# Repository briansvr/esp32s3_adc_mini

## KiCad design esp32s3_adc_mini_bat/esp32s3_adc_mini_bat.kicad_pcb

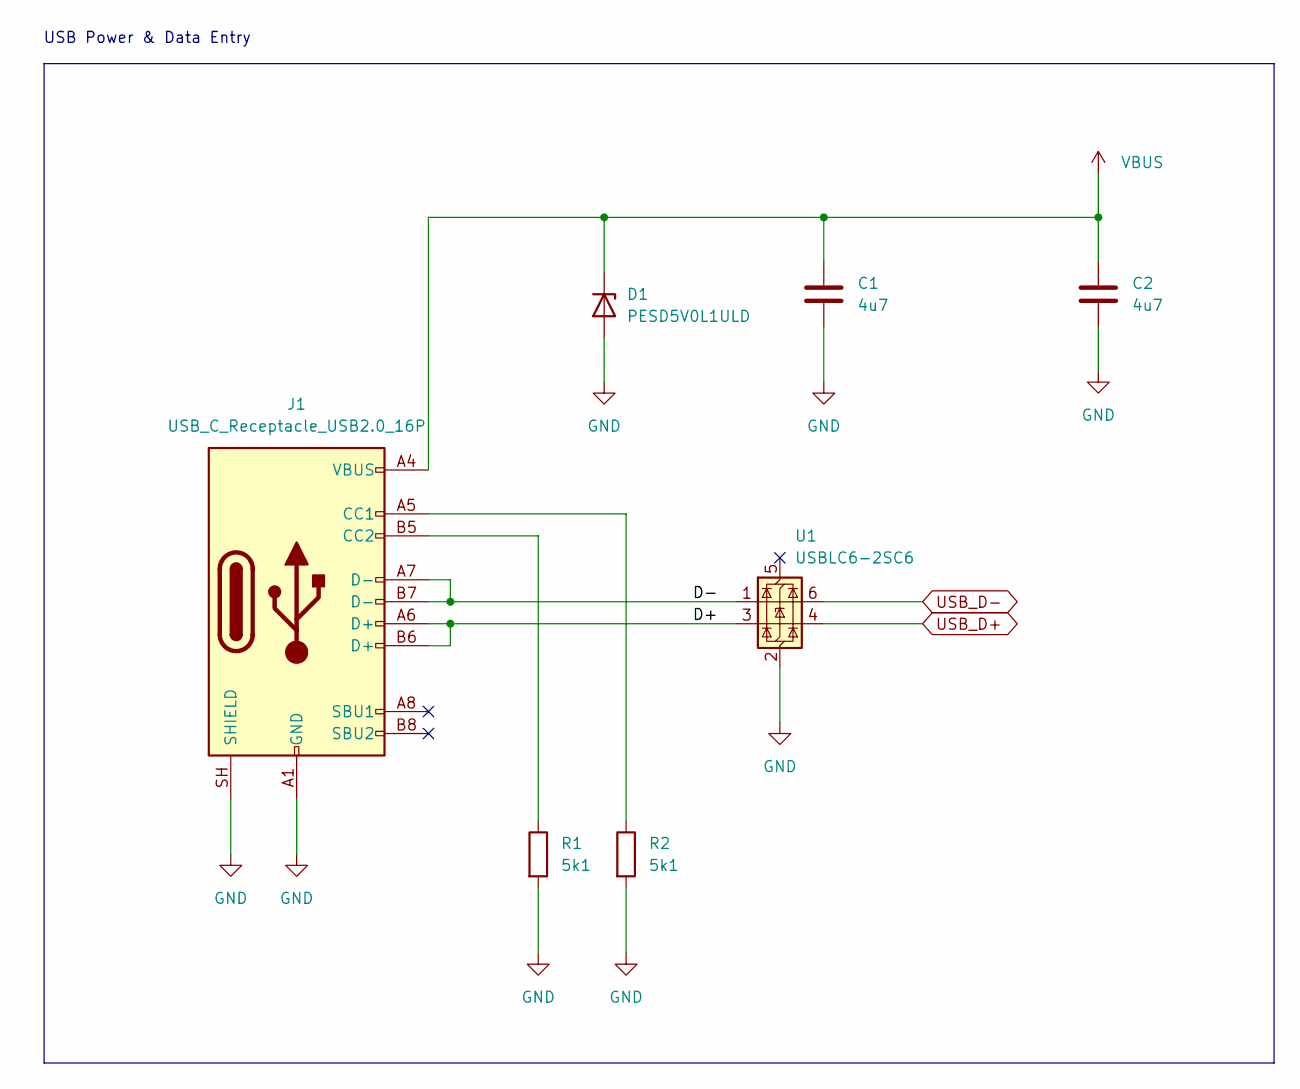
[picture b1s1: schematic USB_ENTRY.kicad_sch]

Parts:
C1, C2: 4u7; C_0805_2012Metric
D1: PESD5V0L1ULD; D_SOD-882D
J1: USB_C_Receptacle_USB2.0_16P; USB_C_Receptacle_G-Switch_GT-USB-7010ASV
R1, R2: 5k1; R_0402_1005Metric
U1: USBLC6-2SC6; SOT-23-6

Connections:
/USB_ENTRY/D+: J1.A6 (D+), J1.B6 (D+), U1.3 (I/O2)
/USB_ENTRY/D-: J1.A7 (D-), J1.B7 (D-), U1.1 (I/O1)
GND: C1.2, C2.2, D1.2 (A), J1.A1 (GND), J1.A12 (GND), J1.B1 (GND), J1.B12 (GND), J1.SH (SHIELD), R1.2, R2.2, U1.2 (GND); also elsewhere on the board
unnamed: J1.A5 (CC1), R2.1
unnamed: J1.B5 (CC2), R1.1
USB_D+: U1.4 (I/O2); also elsewhere on the board
USB_D-: U1.6 (I/O1); also elsewhere on the board
VBUS: C1.1, C2.1, D1.1 (K), J1.A4 (VBUS), J1.A9 (VBUS), J1.B4 (VBUS), J1.B9 (VBUS); also elsewhere on the board

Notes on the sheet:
USB Power & Data Entry

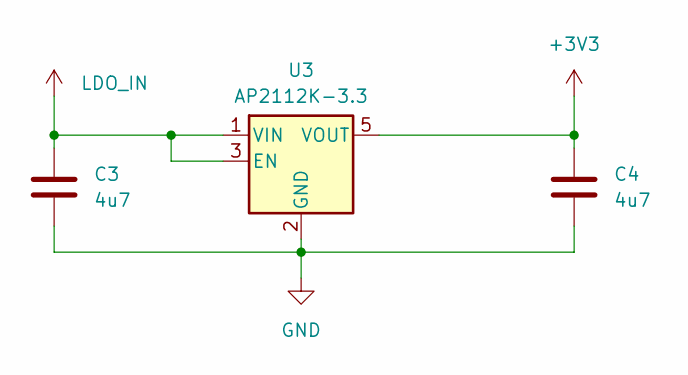
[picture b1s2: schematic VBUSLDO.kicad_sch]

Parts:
C3, C4: 4u7; C_0805_2012Metric
U3: AP2112K-3.3; SOT-23-5

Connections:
+3V3: C4.1, U3.5 (VOUT); also elsewhere on the board
GND: C3.2, C4.2, U3.2 (GND); also elsewhere on the board
LDO_IN: C3.1, U3.1 (VIN), U3.3 (EN); also elsewhere on the board

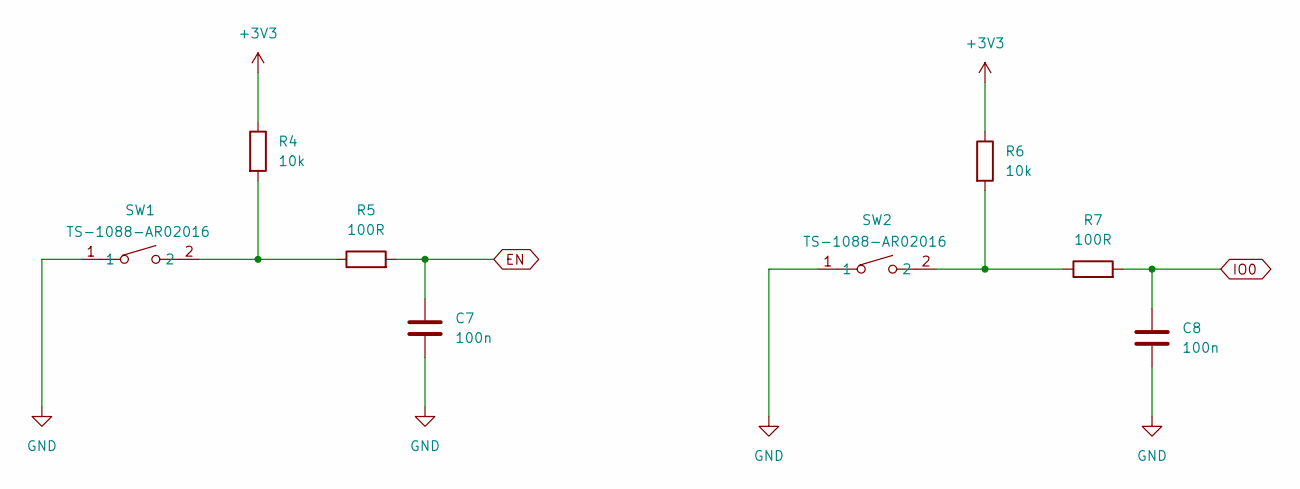
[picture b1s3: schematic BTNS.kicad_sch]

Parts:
C7, C8: 100n; C_0805_2012Metric
R4, R6: 10k; R_0402_1005Metric
R5, R7: 100R; R_0402_1005Metric
SW1, SW2: TS-1088-AR02016; SW-SMD_L3.9-W3.0-P4.45; MPN TS-1088-AR02016; LCSC Part C720477

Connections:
+3V3: R4.1, R6.1; also elsewhere on the board
EN: C7.1, R5.2; also elsewhere on the board
GND: C7.2, C8.2, SW1.1, SW2.1; also elsewhere on the board
IO0: C8.1, R7.2; also elsewhere on the board
unnamed 47: R4.2, R5.1, SW1.2; also elsewhere on the board
unnamed 48: R6.2, R7.1, SW2.2; also elsewhere on the board

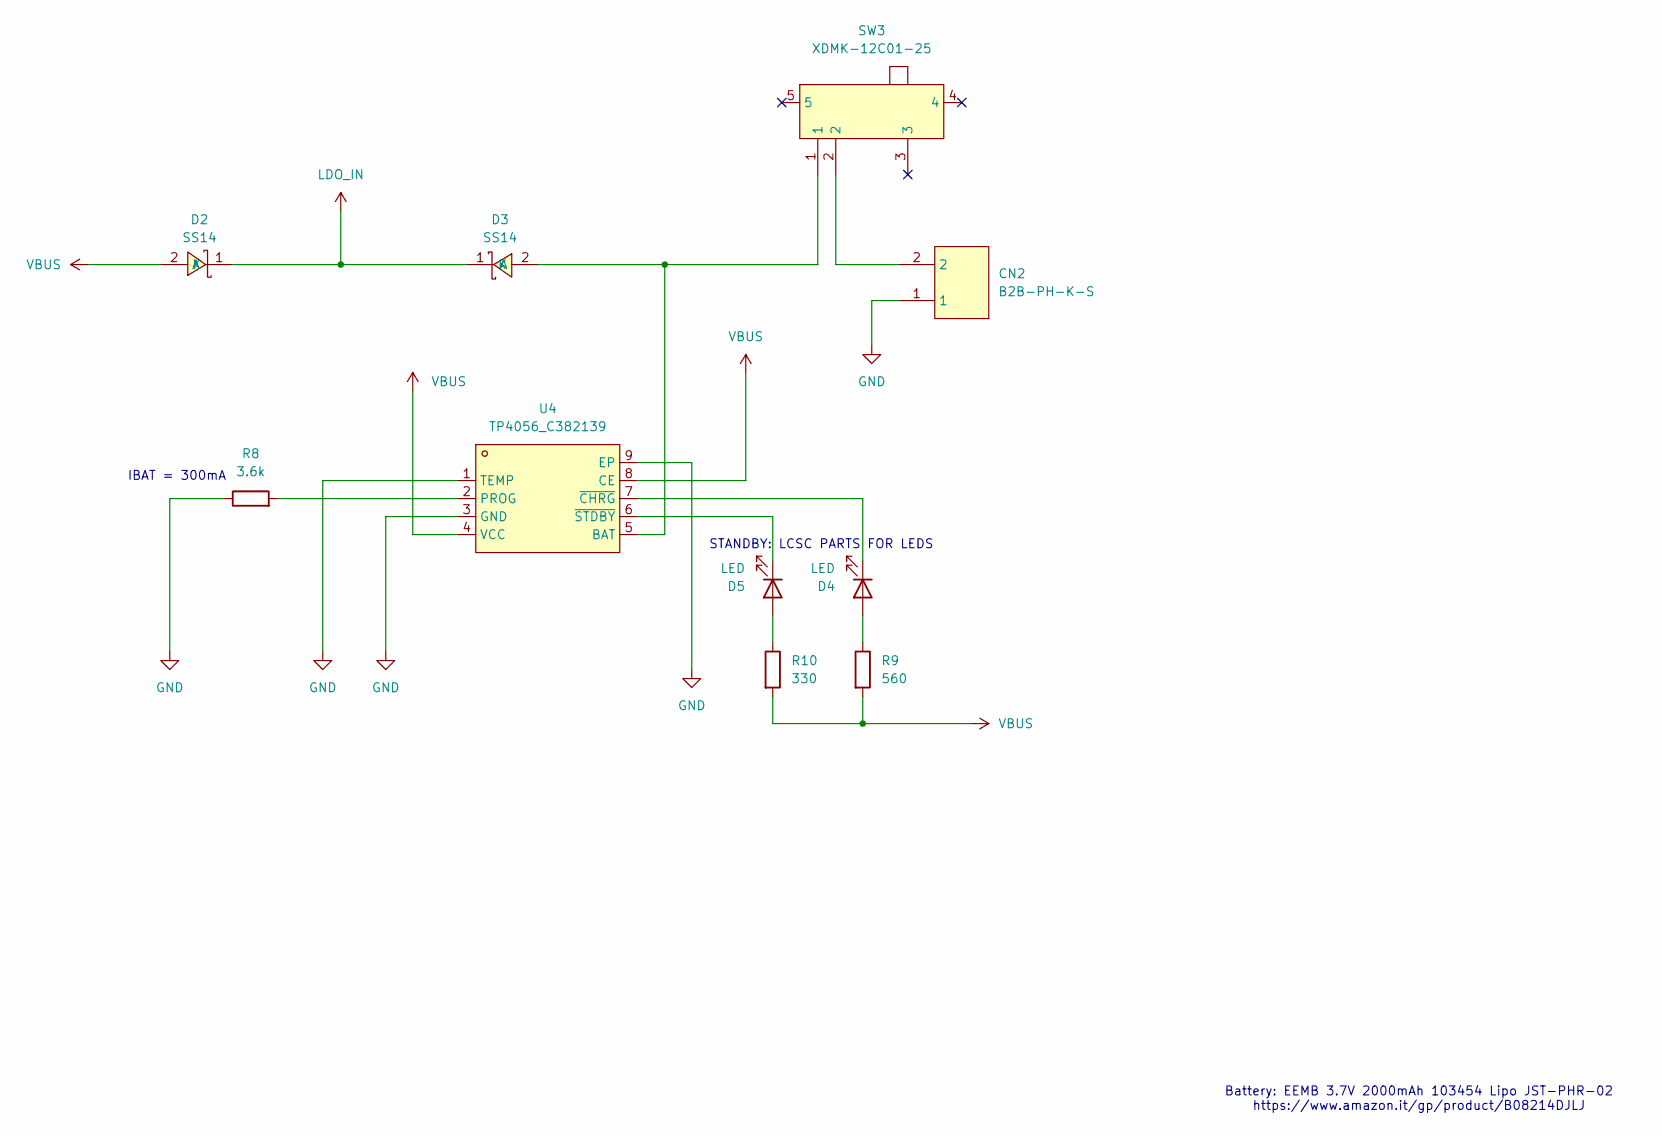
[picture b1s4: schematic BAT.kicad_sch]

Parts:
CN2: B2B-PH-K-S; CONN-TH_B2B-PH-K-S; MPN B2B-PH-K-S(LF)(SN); LCSC Part C131337
D2, D3: SS14; SMA_L4.2-W2.6-LS5.0-RD_1; MPN SS14; LCSC Part C2480
D4, D5: LED; LED_0402_1005Metric
R8: 3.6k; R_0402_1005Metric
R9: 560; R_0402_1005Metric
R10: 330; R_0402_1005Metric
SW3: XDMK-12C01-25; SW-SMD_XDMK-12C01-25; MPN XDMK-12C01-25; LCSC Part C7498220
U4: TP4056_C382139; ESOP-8_L4.9-W3.9-P1.27-LS6.0-BL-EP; MPN TP4056; LCSC Part C382139

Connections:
GND: CN2.1, R8.1, U4.1 (TEMP), U4.3 (GND), U4.9 (EP); also elsewhere on the board
LDO_IN: D2.1 (K), D3.1 (K); also elsewhere on the board
unnamed 39: CN2.2, SW3.2; also elsewhere on the board
unnamed 40: D3.2 (A), SW3.1, U4.5 (BAT); also elsewhere on the board
unnamed: D4.2 (A), R9.1
unnamed: D4.1 (K), U4.7 (~CHRG)
unnamed: D5.2 (A), R10.1
unnamed: D5.1 (K), U4.6 (~STDBY)
unnamed: R8.2, U4.2 (PROG)
VBUS: D2.2 (A), R9.2, R10.2, U4.4 (VCC), U4.8 (CE); also elsewhere on the board

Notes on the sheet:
IBAT = 300mA
Battery: EEMB 3.7V 2000mAh 103454 Lipo JST-PHR-02 https://www.amazon.it/gp/product/B08214DJLJ
STANDBY: LCSC PARTS FOR LEDS

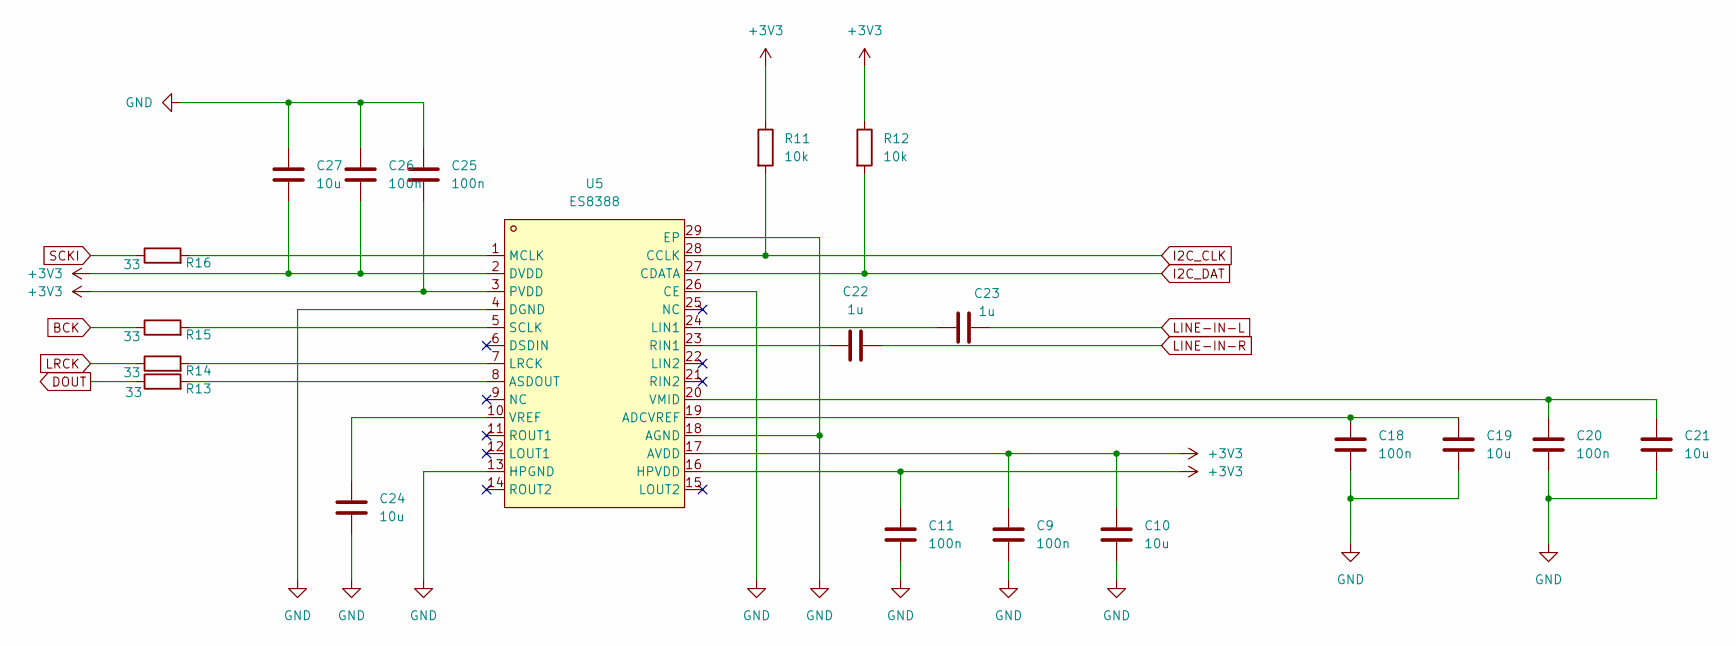
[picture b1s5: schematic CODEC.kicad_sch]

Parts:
C9, C11, C18, C20, C25, C26: 100n; C_0402_1005Metric
C10, C19, C21, C24, C27: 10u; C_0603_1608Metric
C22, C23: 1u; C_0805_2012Metric
R11, R12: 10k; R_0402_1005Metric
R13, R14, R15, R16: 33; R_0402_1005Metric
U5: ES8388; QFN-28_L4.0-W4.0-P0.45-BL-EP; MPN ES8388; LCSC Part C365736

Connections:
+3V3: C9.1, C10.1, C11.1, C25.2, C26.2, C27.2, R11.1, R12.1, U5.2 (DVDD), U5.3 (PVDD), U5.16 (HPVDD), U5.17 (AVDD); also elsewhere on the board
BCK: R15.1; also elsewhere on the board
DOUT: R13.1; also elsewhere on the board
GND: C9.2, C10.2, C11.2, C18.2, C19.2, C20.2, C21.2, C24.2, C25.1, C26.1, C27.1, U5.4 (DGND), U5.13 (HPGND), U5.18 (AGND), U5.26 (CE), U5.29 (EP); also elsewhere on the board
I2C_CLK: R11.2, U5.28 (CCLK); also elsewhere on the board
I2C_DAT: R12.2, U5.27 (CDATA); also elsewhere on the board
LINE-IN-L: C23.1; also elsewhere on the board
LINE-IN-R: C22.1; also elsewhere on the board
LRCK: R14.1; also elsewhere on the board
unnamed: C18.1, C19.1, U5.19 (ADCVREF)
unnamed: R13.2, U5.8 (ASDOUT)
unnamed: C23.2, U5.24 (LIN1)
unnamed: R14.2, U5.7 (LRCK)
unnamed: R16.2, U5.1 (MCLK)
unnamed: C22.2, U5.23 (RIN1)
unnamed: R15.2, U5.5 (SCLK)
unnamed: C20.1, C21.1, U5.20 (VMID)
unnamed: C24.1, U5.10 (VREF)
SCKI: R16.1; also elsewhere on the board

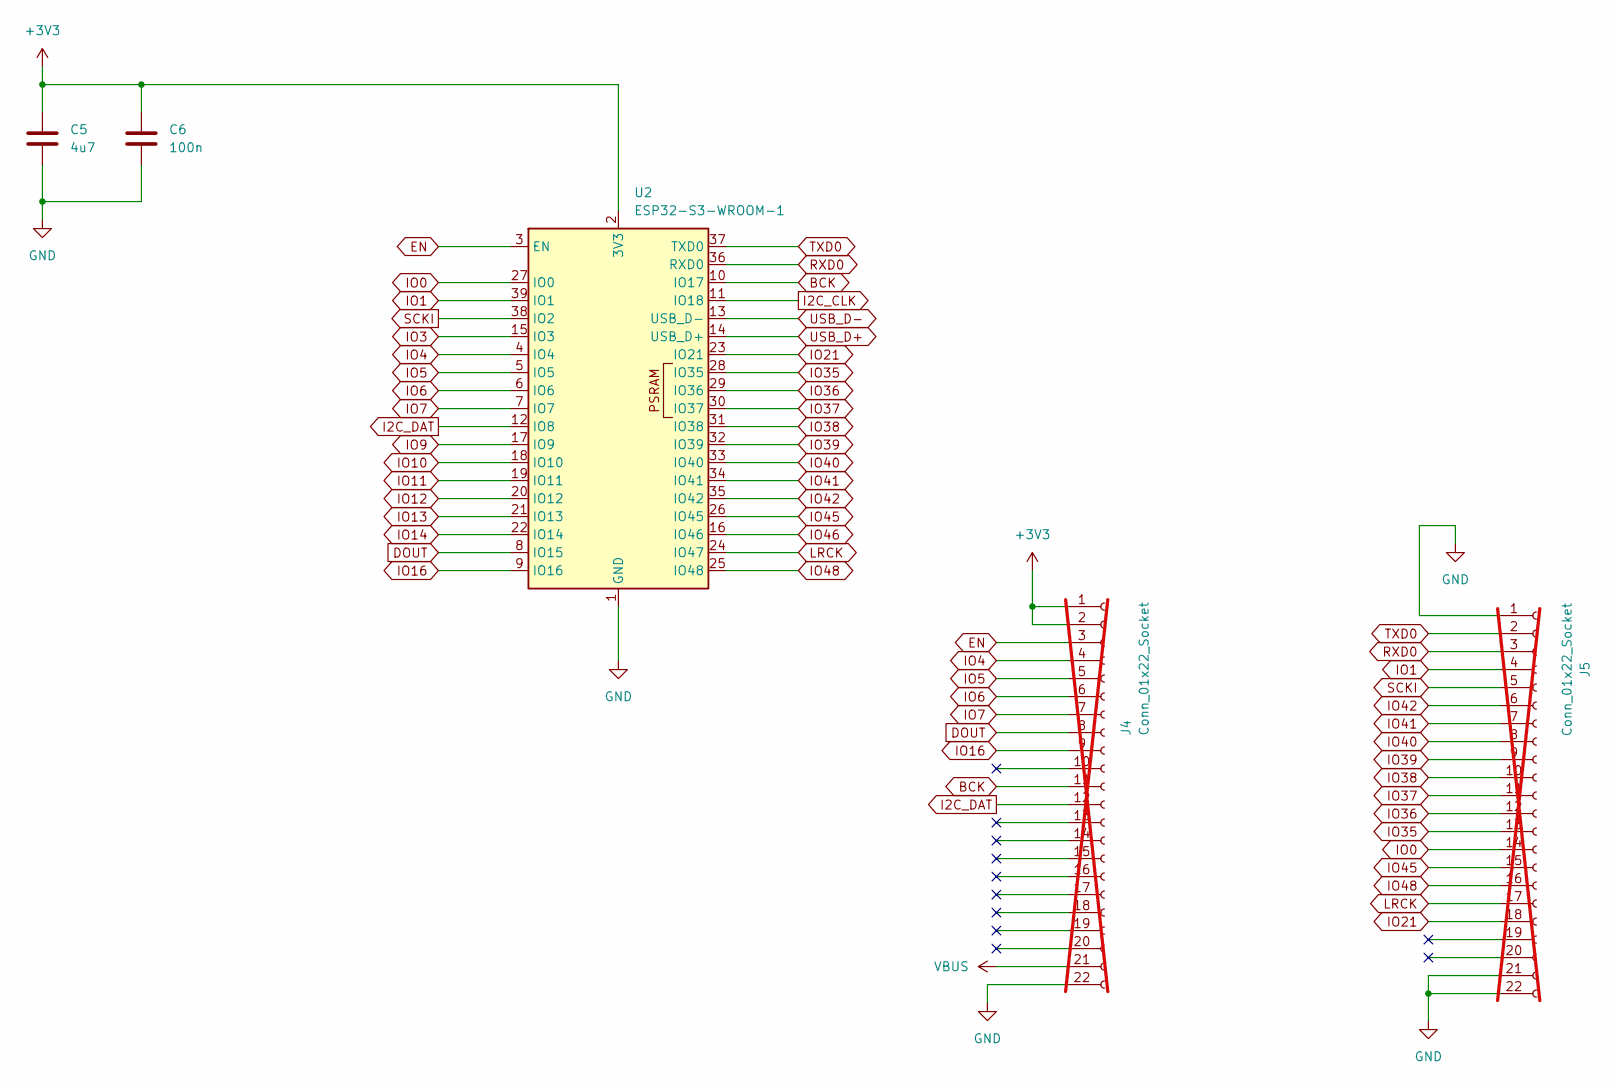
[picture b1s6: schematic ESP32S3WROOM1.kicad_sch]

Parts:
C5: 4u7; C_0805_2012Metric
C6: 100n; C_0805_2012Metric
J4, J5: Conn_01x22_Socket; PinHeader_1x22_P1.00mm_Vertical; not fitted
U2: ESP32-S3-WROOM-1

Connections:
+3V3: C5.1, C6.1, J4.1, J4.2, U2.2 (3V3); also elsewhere on the board
BCK: J4.11, U2.10 (IO17); also elsewhere on the board
DOUT: J4.8, U2.8 (IO15); also elsewhere on the board
EN: J4.3, U2.3 (EN); also elsewhere on the board
GND: C5.2, C6.2, J4.22, J5.1, J5.21, J5.22, U2.1 (GND), U2.40 (GND), U2.41 (GND); also elsewhere on the board
I2C_CLK: U2.11 (IO18); also elsewhere on the board
I2C_DAT: J4.12, U2.12 (IO8); also elsewhere on the board
IO0: J5.14, U2.27 (IO0); also elsewhere on the board
IO1: J5.4, U2.39 (IO1)
IO3: U2.15 (IO3)
IO4: J4.4, U2.4 (IO4)
IO5: J4.5, U2.5 (IO5)
IO6: J4.6, U2.6 (IO6)
IO7: J4.7, U2.7 (IO7)
IO9: U2.17 (IO9)
IO10: U2.18 (IO10)
IO11: U2.19 (IO11)
IO12: U2.20 (IO12)
IO13: U2.21 (IO13)
IO14: U2.22 (IO14)
IO16: J4.9, U2.9 (IO16)
IO21: J5.18, U2.23 (IO21)
IO35: J5.13, U2.28 (IO35)
IO36: J5.12, U2.29 (IO36)
IO37: J5.11, U2.30 (IO37)
IO38: J5.10, U2.31 (IO38)
IO39: J5.9, U2.32 (IO39)
IO40: J5.8, U2.33 (IO40)
IO41: J5.7, U2.34 (IO41)
IO42: J5.6, U2.35 (IO42)
IO45: J5.15, U2.26 (IO45)
IO46: U2.16 (IO46)
IO48: J5.16, U2.25 (IO48)
LRCK: J5.17, U2.24 (IO47); also elsewhere on the board
RXD0: J5.3, U2.36 (RXD0)
SCKI: J5.5, U2.38 (IO2); also elsewhere on the board
TXD0: J5.2, U2.37 (TXD0)
USB_D+: U2.14 (USB_D+); also elsewhere on the board
USB_D-: U2.13 (USB_D-); also elsewhere on the board
VBUS: J4.21; also elsewhere on the board

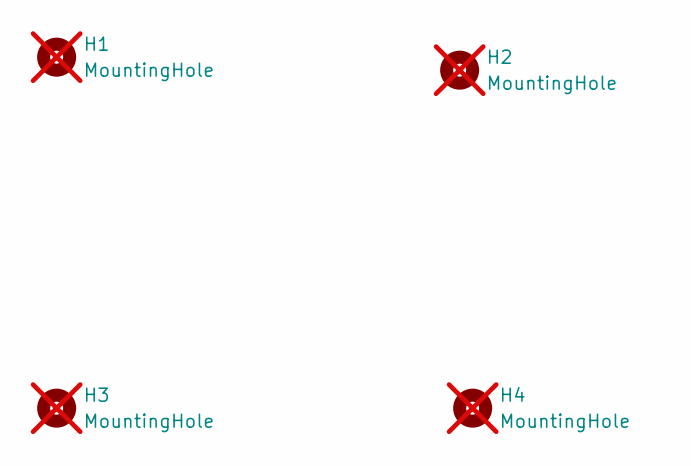
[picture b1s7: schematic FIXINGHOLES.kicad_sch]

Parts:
H1, H2, H3, H4: MountingHole; MountingHole_3.5mm; not fitted

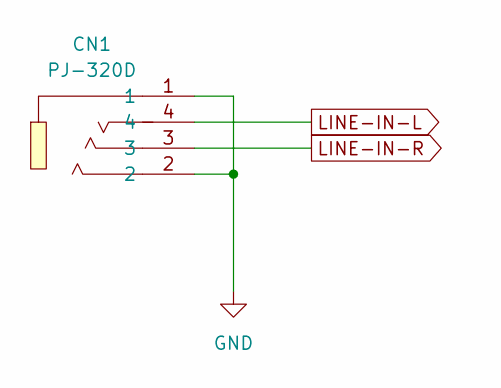
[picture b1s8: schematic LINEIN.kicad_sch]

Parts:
CN1: PJ-320D; AUDIO-SMD_PJ-320D-1; MPN PJ-320D; LCSC Part C431535

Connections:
GND: CN1.1, CN1.2; also elsewhere on the board
LINE-IN-L: CN1.4; also elsewhere on the board
LINE-IN-R: CN1.3; also elsewhere on the board

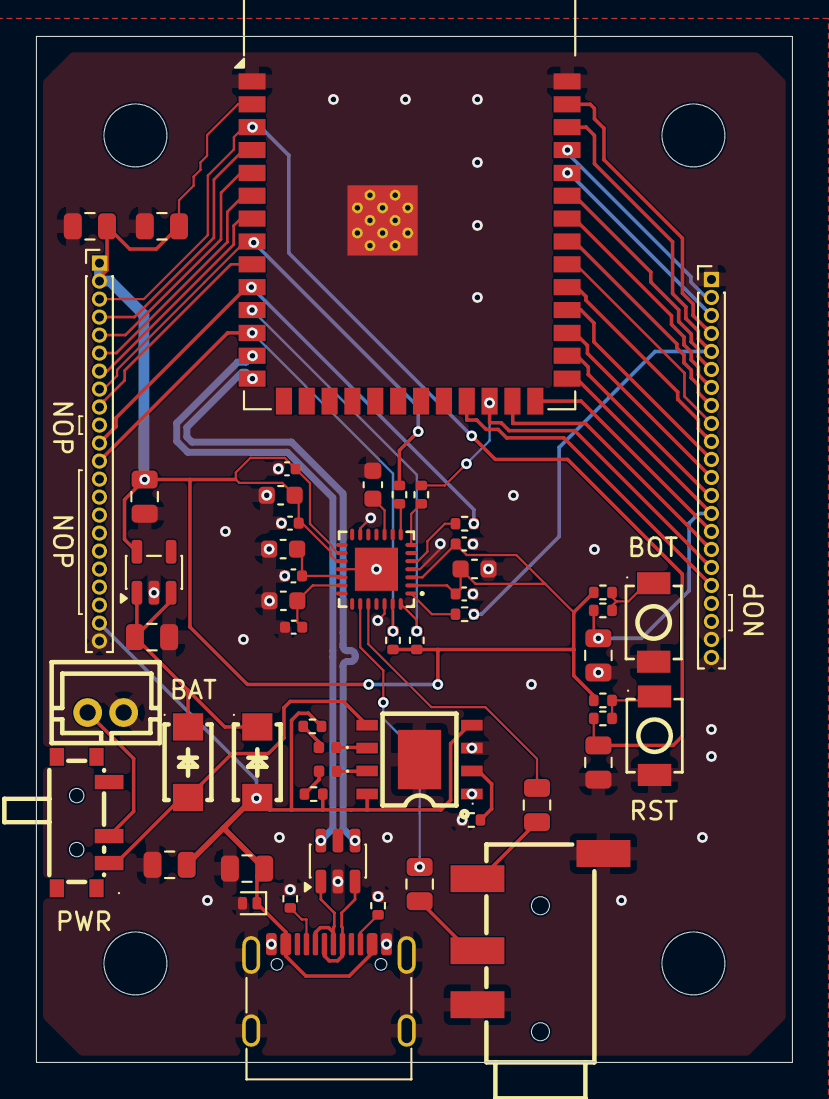
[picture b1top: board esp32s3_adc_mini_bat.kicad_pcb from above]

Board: 2 copper layers, 42.0 x 57.0 mm, 58 parts (0 on the bottom side), 57 nets.

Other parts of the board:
BAT: B2B-PH-K-S; CONN-TH_B2B-PH-K-S
BOT: TS-1088-AR02016; SW-SMD_L3.9-W3.0-P4.45
PWR: XDMK-12C01-25; SW-SMD_XDMK-12C01-25
RST: TS-1088-AR02016; SW-SMD_L3.9-W3.0-P4.45

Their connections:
GND: BAT.1, BOT.1, RST.1; also elsewhere on the board
unnamed 39: BAT.2, PWR.2; also elsewhere on the board
unnamed 40: PWR.1; also elsewhere on the board
unnamed 47: RST.2; also elsewhere on the board
unnamed 48: BOT.2; also elsewhere on the board

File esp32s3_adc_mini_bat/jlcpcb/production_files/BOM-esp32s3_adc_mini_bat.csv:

Comment,Designator,Footprint,LCSC,Quantity
100R,"R5,R7",R_0402_1005Metric,C25076,2
100n,"C11,C18,C20,C25,C26,C9",C_0402_1005Metric,C1525,6
100n,"C6,C7,C8",C_0805_2012Metric,C28233,3
10k,"R11,R12,R4,R6",R_0402_1005Metric,C25744,4
10u,"C10,C19,C21,C24,C27",C_0603_1608Metric,C19702,5
1u,"C22,C23",C_0805_2012Metric,C28323,2
3.6k,R8,R_0402_1005Metric,C25891,1
33,"R13,R14,R15,R16",R_0402_1005Metric,C25105,4
330,R10,R_0402_1005Metric,C25104,1
4u7,"C1,C2,C3,C4,C5",C_0805_2012Metric,C1779,5
560,R9,R_0402_1005Metric,C25126,1
5k1,"R1,R2",R_0402_1005Metric,C25905,2
ES8388,U5,QFN-28_L4.0-W4.0-P0.45-BL-EP,C365736,1
LED,D4,LED_0402_1005Metric,C71911,1
LED,D5,LED_0402_1005Metric,C74338,1
PESD5V0L1ULD,D1,D_SOD-882D,C552557,1
SS14,"D2,D3",SMA_L4.2-W2.6-LS5.0-RD_1,C2480,2
TS-1088-AR02016,"BOT,RST",SW-SMD_L3.9-W3.0-P4.45,C720477,2

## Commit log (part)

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2026-05-14 chore: init
2026-05-15 feat: ES8388
2026-05-15 feat: schematic done and pcb grouping
2026-06-09 chore: GNU General Public License v3
